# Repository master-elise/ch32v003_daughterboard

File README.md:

See https://www.sameskydevices.com/product/resource/3dmodel/ptn091-v05115k1b found at https://eu.mouser.com/ProductDetail/Same-Sky/PTN091-V05115K1B?qs=IKkN%2F947nfCwGg20YudwyA%3D%3D

See https://www.olimex.com/Products/RISC-V/WCH-CH32V003EVT/

## Using https://github.com/cnlohr/ch32fun

The proposed toolchain is compiled with https://github.com/master-elise/summon-arm-toolchain and its ``summon-riscv-toolchain`` script. The resulting toolchain will be located in ``$HOME/svt`` so that ``$HOME/svt/bin`` must be added to the ``$PATH`` to be used.

The ``ch32fun.mk`` from https://github.com/cnlohr/ch32fun is updated by replacing 
```
PREFIX_DEFAULT:=riscv64-elf
```
with
```
PREFIX_DEFAULT:=riscv32-elf
```
and removing 
```
ifneq ($(shell $(WHICH) riscv64-unknown-elf-gcc 2>$(NULLDEV)),)
        PREFIX_DEFAULT:=riscv64-unknown-elf
else ifneq ($(shell $(WHICH) riscv-none-elf-gcc 2>$(NULLDEV)),)
        PREFIX_DEFAULT:=riscv-none-elf
else ifneq ($(shell $(WHICH) riscv64-linux-gnu-gcc 2>$(NULLDEV)),)
        PREFIX_DEFAULT:=riscv64-linux-gnu
else ifeq ($(OS_NAME),netbsd)
        # assume using pkgsrc/cross/riscv64-none-elf-gcc and
        # pkgsrc/cross/riscv64-none-elf-binutils
        PKGSRC_LOCALBASE ?= /usr/pkg
        ifneq ($(wildcard $(PKGSRC_LOCALBASE)/cross-riscv64-none-elf/bin/riscv64-none-elf-gcc),)
                PREFIX_DEFAULT := $(PKGSRC_LOCALBASE)/cross-riscv64-none-elf/bin/riscv64-none-elf
        endif
endif
```
which would otherwise overwrite our change.

To check, goto
```
cd ch32fun/examples/gpio_and_adc
make
```
must conclude with
```
riscv32-elf-objdump -S gpio_and_adc.elf > gpio_and_adc.lst
riscv32-elf-objcopy -R .storage  -O binary gpio_and_adc.elf gpio_and_adc.bin
riscv32-elf-objcopy -j .storage -O binary gpio_and_adc.elf gpio_and_adc_ext.bin
riscv32-elf-objcopy -O ihex gpio_and_adc.elf gpio_and_adc.hex
../../ch32fun//../minichlink/minichlink -w gpio_and_adc.bin flash -b
```
and ``minichlink`` might or might not fail depending on the programmer available on the computer. When using the Atmega32U4-based programmer found in ``arduino-ch32v003-swio``, replace the programming command with
```
../../minichlink/minichlink -c /dev/ttyUSB0 -C ardulink -w gpio_and_adc.bin flash -b
```

## Example of a GDB session using the ardulink interface

Terminal 1:
```
ch32fun/examples/gpio_and_adc$ ../../minichlink/minichlink -c /dev/ttyUSB0 -C ardulink -G
minichlink version - 8e9d331abce4f0aff5fc4f1c162844bff76fbf28
Opening serial port /dev/ttyUSB0 at 115200 baud.
Ardulink: synced.
Ardulink: target power 1
Interface Setup
Detected CH32V003
Flash Storage: 16 kB
Part UUID: 9b-77-ab-cd-04-72-bd-2e
Part Type: 00-30-05-10
Read protection: disabled
gdbserver running on port 3333
GDBServer Running
```

Terminal 2:
```
ch32fun/examples/gpio_and_adc$ gdb-multiarch -q gpio_and_adc.elf
(gdb) target remote localhost:3333
Remote debugging using localhost:3333
0x00000862 in DelaySysTick (n=6000000) at ../../ch32fun/ch32fun.c:1884
1884            while( ((int32_t)( SysTick->CNT - targend )) < 0 );
(gdb) list main
...
(gdb) list
...
(gdb) list
...
60                      printf( "1: %d %d %d %d\n",
(gdb) break 60
Breakpoint 1 at 0x7d8: file ch32fun/examples/gpio_and_adc/gpio_and_adc.c, line 60.
(gdb) continue
Continuing.

Breakpoint 1, main () at ch32fun/examples/gpio_and_adc/gpio_and_adc.c:60
60                      printf( "1: %d %d %d %d\n",
(gdb) bt
#0  main () at ch32fun/examples/gpio_and_adc/gpio_and_adc.c:60
(gdb) print $sp
$1 = (void *) 0x200007e8
```

## Using the Debian binary toolchain
The baremetal toolchain ``sudo apt install gcc-riscv64-unknown-elf`` can be used to compile the ``ch32fun`` examples, but care must be taken about
```
NEWLIB?=/usr/include/newlib
```
in ``ch32fun/ch32fun.mk`` since Debian no longer supports Newlib and lacking this directory, the compiler searches
for alternative ``stdio.h`` in ``/usr/include``. The Linux (operating system) ``stdio.h`` definition is incompatible with
the baremetal definition and leads to the error
```
../../ch32fun//ch32fun.c:1652:10: error: expected declaration specifiers or '...' before 'stdout'
```
This is solved by using the ``stdio.h`` of any Newlib source code, e.g.
```
NEWLIB=.../stm32/ZephyrOS/modules/lib/picolibc/newlib/libc/stdio/
```
since I happen to have a Newlib install from ZephyrOS, but also valid by installing the last newlib-related package in
Debian named ``sudo apt install libnewlib-sh-elf-dev`` and in this case
```
NEWLIB=/usr/sh-elf/include
```
In both cases the compilation succeeds with
```
ch32fun/examples/gpio_and_adc$ make
riscv64-unknown-elf-gcc -E -P -x c -DTARGET_MCU=CH32V003 -DMCU_PACKAGE=1 -DTARGET_MCU_LD=0 -DTARGET_MCU_MEMORY_SPLIT= ../../ch32fun//ch32fun.ld > ../../ch32fun//generated__.ld
riscv64-unknown-elf-gcc -o gpio_and_adc.elf ../../ch32fun//ch32fun.c gpio_and_adc.c   -g -Os -flto -ffunction-sections -fdata-sections -fmessage-length=0 -msmall-data-limit=8 -fno-tree-loop-distribute-patterns -march=rv32ec -mabi=ilp32e -DCH32V003 -static-libgcc -I../../ch32fun//../extralibs -I.../stm32/ZephyrOS/modules/lib/picolibc/newlib/libc/stdio// -I../../ch32fun/ -nostdlib -I. -Wall  -Wl,--print-memory-usage -Wl,-Map=gpio_and_adc.map -L../../ch32fun//../misc -lgcc -lgcc -T ../../ch32fun//generated__.ld -Wl,--gc-sections
Memory region         Used Size  Region Size  %age Used
           FLASH:        2124 B        16 KB     12.96%
             RAM:           0 B         2 KB      0.00%
riscv64-unknown-elf-objdump -S gpio_and_adc.elf > gpio_and_adc.lst
riscv64-unknown-elf-objcopy -R .storage  -O binary gpio_and_adc.elf gpio_and_adc.bin
riscv64-unknown-elf-objcopy -j .storage -O binary gpio_and_adc.elf gpio_and_adc_ext.bin
riscv64-unknown-elf-objcopy -O ihex gpio_and_adc.elf gpio_and_adc.hex
```

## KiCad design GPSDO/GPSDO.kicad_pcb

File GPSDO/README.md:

For using the external resonator, see ``ch32fun/examples/external_crystal`` and set
```
#define FUNCONF_USE_HSE 1               // Use External Oscillator
#define FUNCONF_USE_PLL 0               // Do not use built-in 2x PLL
```
in ``funconfig.h``, verified since short circuiting the cystal resonator stops 
the LED from blinking.

Check watchdog timer in ``ch32fun/examples/iwdg``.

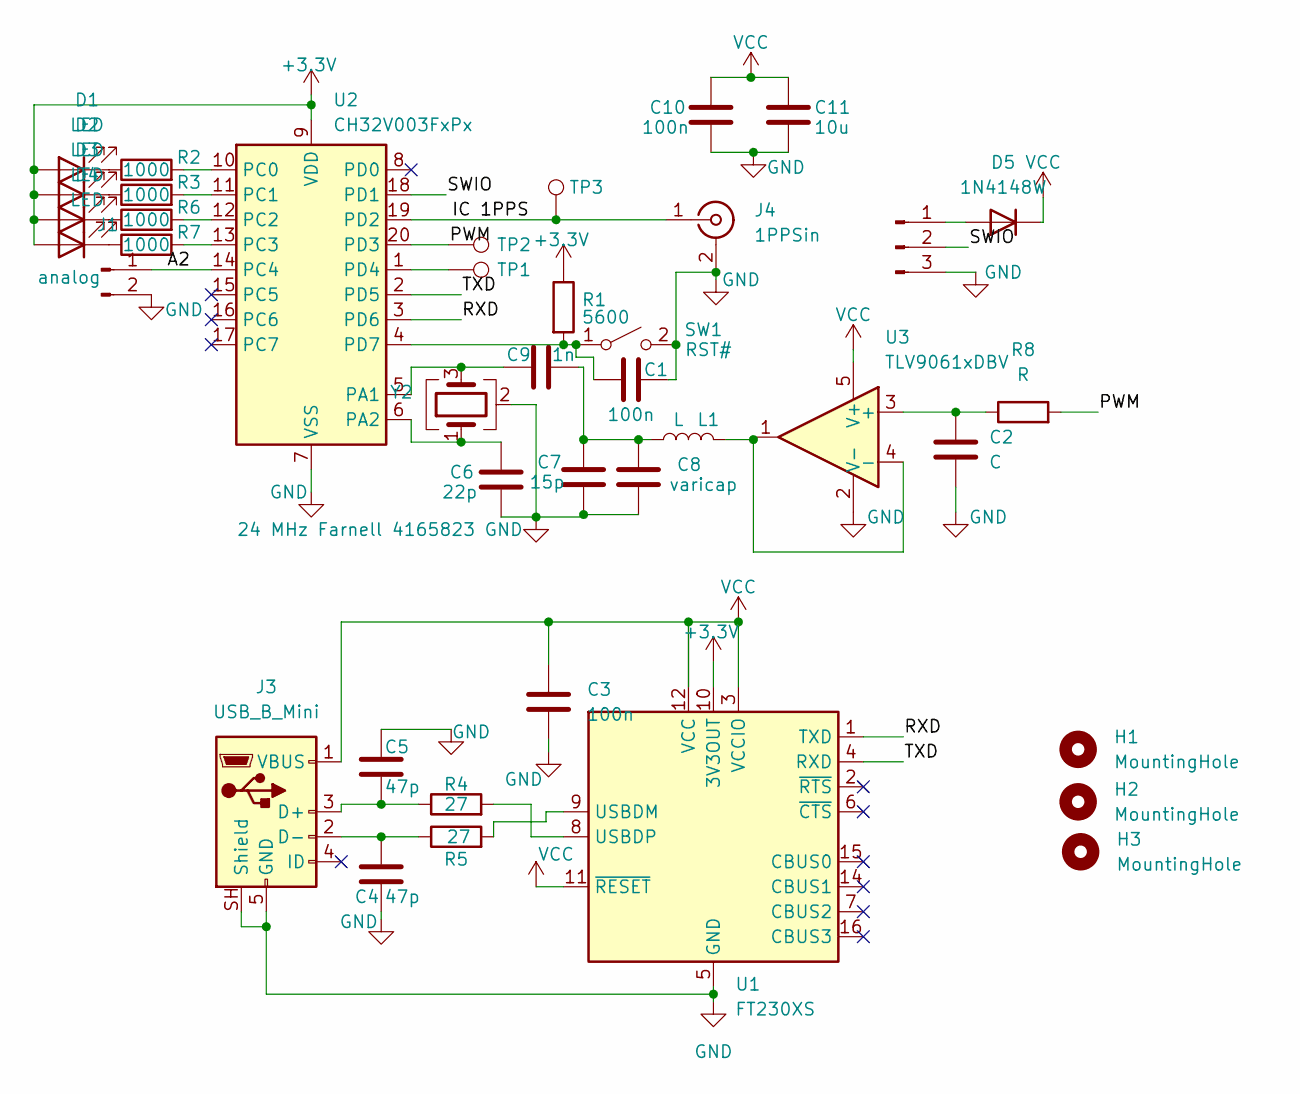
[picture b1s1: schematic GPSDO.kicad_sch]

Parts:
C1, C3, C10: 100n; C_0805_2012Metric_Pad1.18x1.45mm_HandSolder
C2: C; C_0805_2012Metric_Pad1.18x1.45mm_HandSolder
C4, C5: 47p; C_0805_2012Metric_Pad1.18x1.45mm_HandSolder
C6: 22p; C_0805_2012Metric_Pad1.18x1.45mm_HandSolder
C7: 15p; C_0805_2012Metric_Pad1.18x1.45mm_HandSolder
C8: varicap; C_0805_2012Metric_Pad1.18x1.45mm_HandSolder
C9: 1n; C_0805_2012Metric_Pad1.18x1.45mm_HandSolder
C11: 10u; C_0805_2012Metric_Pad1.18x1.45mm_HandSolder
D1, D2, D3, D4: LED; LED_0805_2012Metric_Pad1.15x1.40mm_HandSolder
D5: 1N4148W; D_SOD-123
H1, H2, H3: MountingHole; MountingHole_2.1mm
J1: analog; PinHeader_1x02_P2.54mm_Vertical
J2: Conn_01x03_Pin; PinSocket_1x03_P2.54mm_Vertical
J3: USB_B_Mini; USB_Mini-B_Lumberg_2486_01_Horizontal
J4: 1PPSin; SMA_Amphenol_901-144_Vertical
L1: L; L_0805_2012Metric_Pad1.05x1.20mm_HandSolder
R1: 5600; R_0805_2012Metric_Pad1.20x1.40mm_HandSolder
R2, R3, R6, R7: 1000; R_0805_2012Metric_Pad1.20x1.40mm_HandSolder
R4, R5: 27; R_0805_2012Metric_Pad1.20x1.40mm_HandSolder
R8: R; R_0805_2012Metric_Pad1.20x1.40mm_HandSolder
SW1: RST#; SW_SPST_B3SL-1002P
TP1, TP2, TP3: TestPoint; TestPoint_Pad_2.5x2.5mm
U1: FT230XS; SSOP-16_3.9x4.9mm_P0.635mm
U2: CH32V003FxPx; TSSOP-20_4.4x6.5mm_P0.65mm
U3: TLV9061xDBV; SOT-23-5
Y2: 24 MHz Farnell 4165823; Crystal_SMD_Abracon_ABM3B-4Pin_5.0x3.2mm

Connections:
+3.3V: D1.2 (A), D2.2 (A), D3.2 (A), D4.2 (A), R1.1, U1.10 (3V3OUT), U2.9 (VDD)
/A2: J1.1, U2.14 (PC4)
/IC 1PPS: J4.1 (In), TP3.1 (1_1), U2.19 (PD2)
/PWM: R8.2, TP2.1 (1_1), U2.20 (PD3)
/RXD: U1.1 (TXD), U2.3 (PD6)
/SWIO: J2.2, U2.18 (PD1)
/TXD: U1.4 (RXD), U2.2 (PD5)
GND: C1.2, C2.2, C3.2, C4.2, C5.1, C6.2, C7.2, C8.2, C10.2, C11.2, J1.2, J2.3, J3.5 (GND), J3.SH (Shield), J4.2 (Ext), SW1.2 (B), U1.5 (GND), U1.13 (GND), U2.7 (VSS), U3.2 (V-), Y2.2 (G), Y2.4 (G)
unnamed: C7.1, C8.1, C9.2, L1.1
unnamed: D1.1 (K), R2.1
unnamed: D2.1 (K), R3.1
unnamed: D3.1 (K), R6.1
unnamed: D4.1 (K), R7.1
unnamed: D5.2 (A), J2.1
unnamed: C5.2, J3.3 (D+), R4.1
unnamed: C4.1, J3.2 (D-), R5.1
unnamed: C1.1, R1.2, SW1.1 (A), U2.4 (PD7)
unnamed: R5.2, U1.9 (USBDM)
unnamed: R4.2, U1.8 (USBDP)
unnamed: C9.1, U2.5 (PA1), Y2.3
unnamed: C6.1, U2.6 (PA2), Y2.1
unnamed: R2.2, U2.10 (PC0)
unnamed: R3.2, U2.11 (PC1)
unnamed: R6.2, U2.12 (PC2)
unnamed: R7.2, U2.13 (PC3)
unnamed: TP1.1 (1_1), U2.1 (PD4)
unnamed: C2.1, R8.1, U3.3 (+)
unnamed: L1.2, U3.1, U3.4 (-)
VCC: C3.1, C10.1, C11.1, D5.1 (K), J3.1 (VBUS), U1.3 (VCCIO), U1.11 (~RESET), U1.12 (VCC), U3.5 (V+)

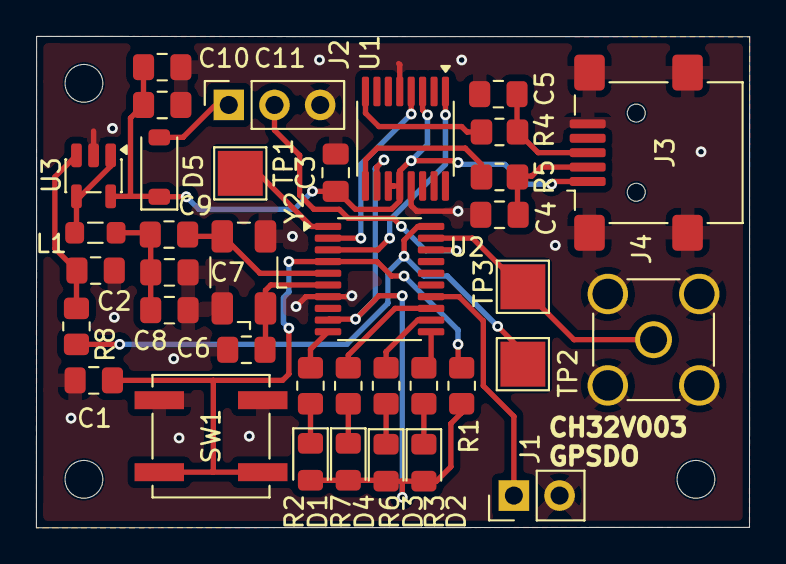
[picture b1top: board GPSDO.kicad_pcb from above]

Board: 2 copper layers, 39.6 x 27.3 mm, 40 parts (0 on the bottom side), 29 nets.

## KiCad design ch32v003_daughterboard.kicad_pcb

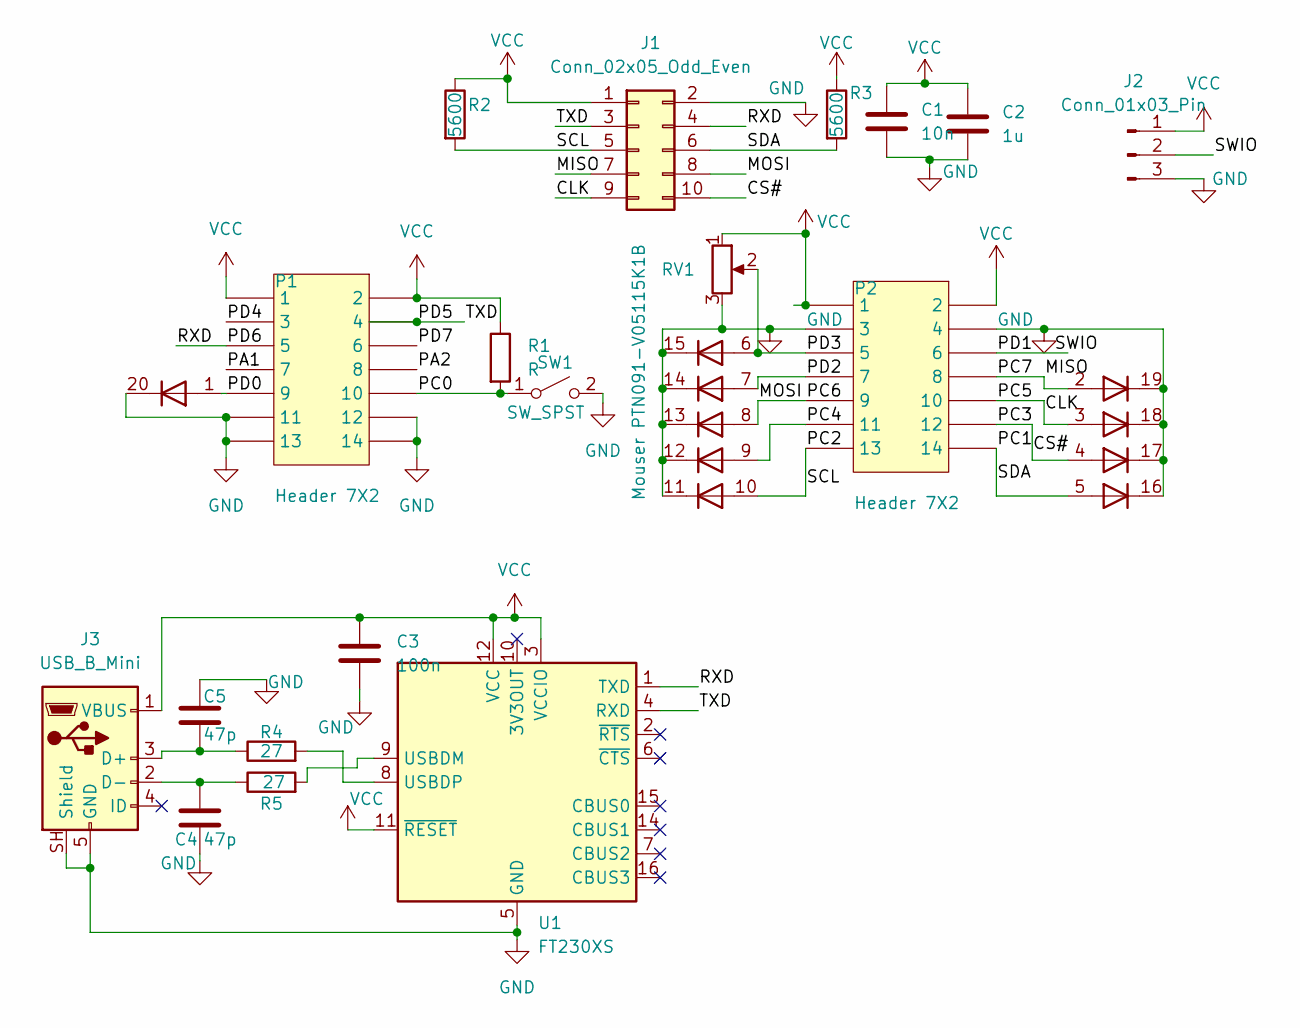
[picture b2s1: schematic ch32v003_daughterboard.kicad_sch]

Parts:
BAR1: HDSP-4850; HDSP-48xx
C1: 10n; C_0805_2012Metric_Pad1.18x1.45mm_HandSolder
C2: 1u; C_0805_2012Metric_Pad1.18x1.45mm_HandSolder
C3: 100n; C_0805_2012Metric_Pad1.18x1.45mm_HandSolder
C4, C5: 47p; C_0805_2012Metric_Pad1.18x1.45mm_HandSolder
J1: Conn_02x05_Odd_Even; PinSocket_2x05_P2.54mm_Vertical
J2: Conn_01x03_Pin; PinSocket_1x03_P2.54mm_Vertical
J3: USB_B_Mini; USB_Mini-B_Lumberg_2486_01_Horizontal
P1, P2: Header 7X2; PinHeader_2x07_P2.54mm_Vertical
R1: R; R_0805_2012Metric_Pad1.20x1.40mm_HandSolder
R2, R3: 5600; R_0805_2012Metric_Pad1.20x1.40mm_HandSolder
R4, R5: 27; R_0805_2012Metric_Pad1.20x1.40mm_HandSolder
RV1: Mouser PTN091-V05115K1B
SW1: SW_SPST; SW_SPST_B3SL-1002P
U1: FT230XS; SSOP-16_3.9x4.9mm_P0.635mm

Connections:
/CLK: BAR1.3 (A), J1.9, P2.10
/CS#: BAR1.4 (A), J1.10, P2.12
/MISO: BAR1.2 (A), J1.7, P2.8
/MOSI: BAR1.8 (A), J1.8, P2.9
/PA1: P1.7
/PA2: P1.8
/PC0: P1.10, R1.2, SW1.1 (A)
/PC1: BAR1.5 (A), J1.6, P2.14, R3.2
/PC2: BAR1.10 (A), J1.5, P2.13, R2.2
/PC4: BAR1.9 (A), P2.11
/PD0: BAR1.1 (A), P1.9
/PD1: J2.2, P2.6
/PD2: BAR1.7 (A), P2.7
/PD3: BAR1.6 (A), P2.5, RV1.2
/PD4: P1.3
/PD5: J1.3, P1.4, U1.4 (RXD)
/PD6: J1.4, P1.5, U1.1 (TXD)
/PD7: P1.6
GND: BAR1.11 (K), BAR1.12 (K), BAR1.13 (K), BAR1.14 (K), BAR1.15 (K), BAR1.16 (K), BAR1.17 (K), BAR1.18 (K), BAR1.19 (K), BAR1.20 (K), C1.2, C2.2, C3.2, C4.2, C5.1, J1.2, J2.3, J3.5 (GND), J3.SH (Shield), P1.11, P1.12, P1.13, P1.14, P2.3, P2.4, RV1.3, SW1.2 (B), U1.5 (GND), U1.13 (GND)
unnamed: C5.2, J3.3 (D+), R4.1
unnamed: C4.1, J3.2 (D-), R5.1
unnamed: R5.2, U1.9 (USBDM)
unnamed: R4.2, U1.8 (USBDP)
VCC: C1.1, C2.1, C3.1, J1.1, J2.1, J3.1 (VBUS), P1.1, P1.2, P2.1, P2.2, R1.1, R2.1, R3.1, RV1.1, U1.3 (VCCIO), U1.11 (~RESET), U1.12 (VCC)

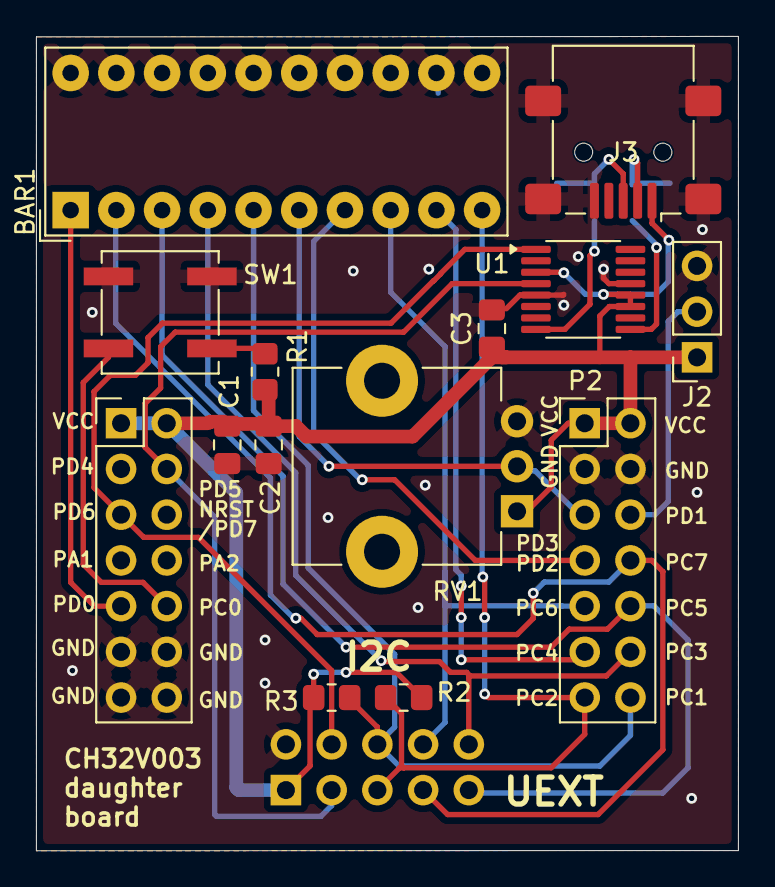
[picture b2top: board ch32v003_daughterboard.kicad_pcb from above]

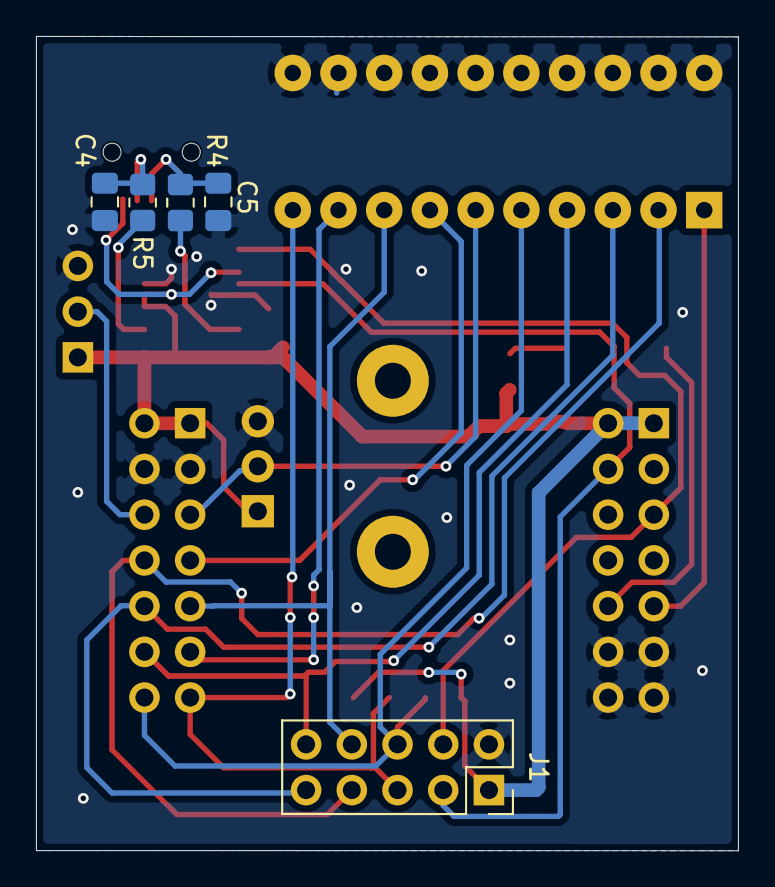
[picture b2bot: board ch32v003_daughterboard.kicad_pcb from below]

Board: 2 copper layers, 39.0 x 45.2 mm, 19 parts (5 on the bottom side), 20 nets.

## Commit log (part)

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2026-06-02 free SDIO + pot.
2026-06-03 add FTDI RS232-USB
2026-06-10 add push button
2026-06-14 programmer functional on Atmega32U4
2026-06-14 typo
2026-06-14 README
2026-06-14 cleanup uart.c
2026-06-14 cleanup main
2026-06-14 picture
2026-06-15 add I2C pullup resistors
2026-06-26 main.c: move power management pin to PD3 (D1)
2026-06-26 Connections 32U4->RV
2026-06-26 connections
2026-06-26 compilation procedure
2026-06-26 programming procedure
2026-06-26 programming
2026-06-26 GDB demo
2026-06-27 minimize differences with original code by setting uart=stdout and cleanup USB additions
2026-06-27 avoid overwriting FTDI stdio definition with UART definition
2026-06-27 return to original main.c now that stdio is properly defined
2026-06-29 add missing passive and decoupling capacitors
2026-06-30 newlib issue when using the Debian baremetal toolchain
2026-06-30 explanation about newlib + realized circuit
